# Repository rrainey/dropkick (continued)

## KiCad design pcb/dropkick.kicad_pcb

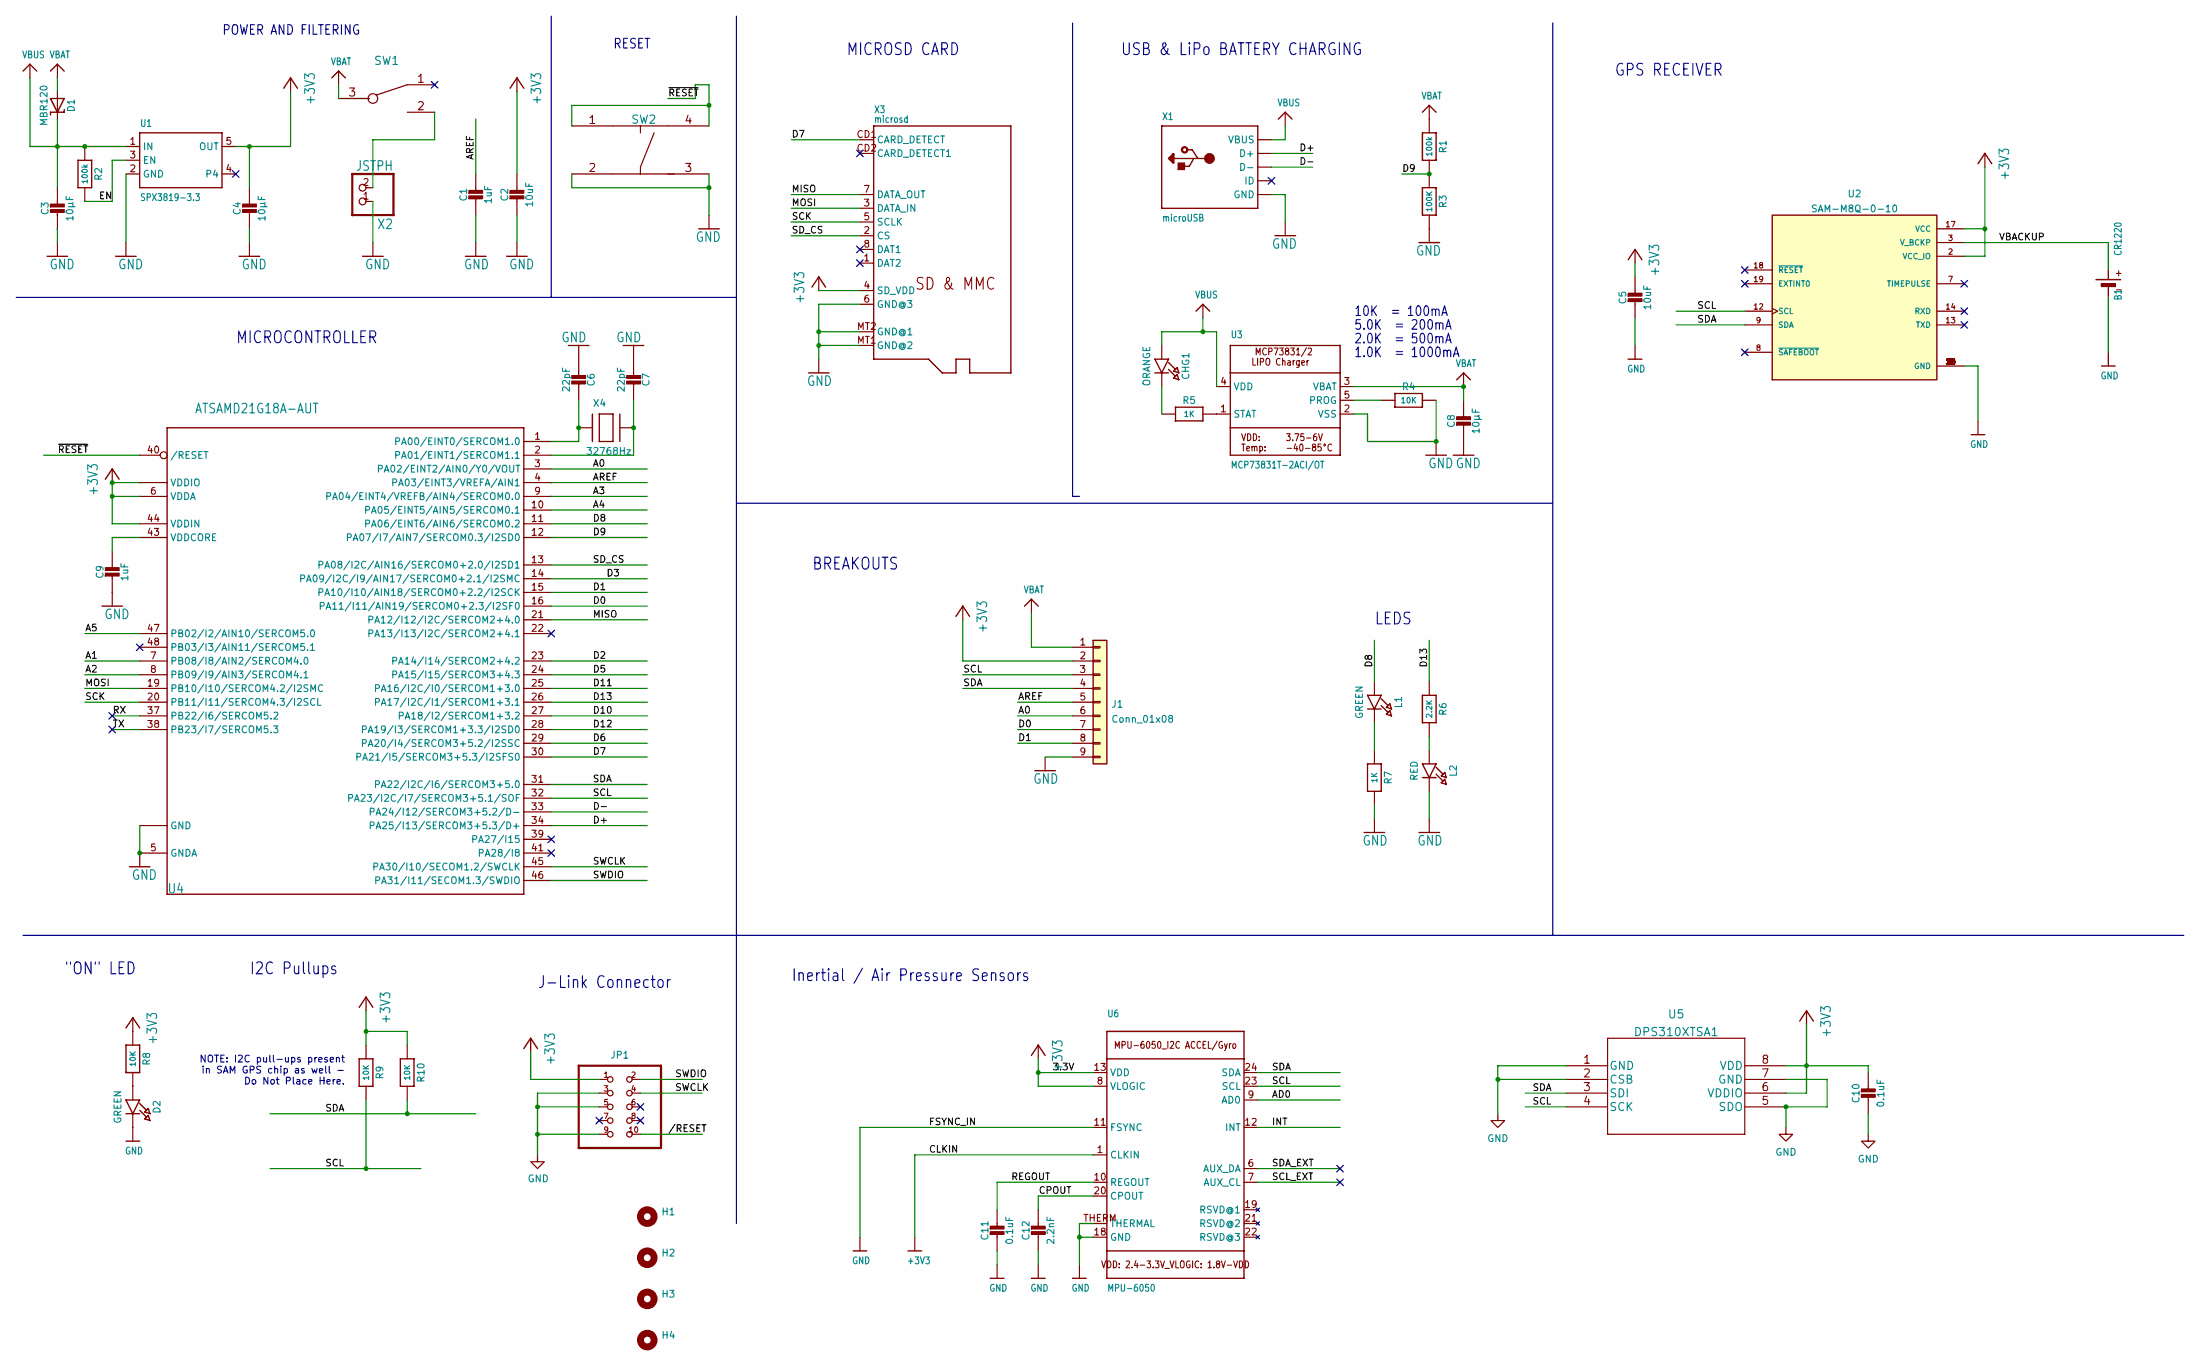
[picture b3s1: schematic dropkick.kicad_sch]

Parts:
B1: CR1220; CR1220-2
C1, C9: 1uF; C_0603_1608Metric
C2, C5: 10uF; C_0805_2012Metric
C3, C4, C8: 10µF; C_0805_2012Metric
C6, C7: 22pF; C_0603_1608Metric
C10: 0.1uF; C_0603_1608Metric
C11: 0.1uF; 0603-NO
C12: 2.2nF; 0603-NO
CHG1: ORANGE; CHIPLED_0603_NOOUTLINE
D1: MBR120; SOD-123
D2: GREEN; CHIPLED_0603_NOOUTLINE
H1, H2, H3, H4: MountingHole; MOUNTINGHOLE_2.5_PLATED
J1: Conn_01x08; PinHeader_1x09_P2.54mm_Vertical
JP1: 3221-10-0300-00-TR
L1: GREEN; CHIPLED_0603_NOOUTLINE
L2: RED; CHIPLED_0603_NOOUTLINE
R1, R2: 100k; 0603-NO
R3: 100K; 0603-NO
R4, R8, R9, R10: 10K; R_0603_1608Metric
R5, R7: 1K; R_0603_1608Metric
R6: 2.2K; R_0603_1608Metric
SW1: 450405020524
SW2: KMR211NG_LFS; KMR211NG LFS
U1: SPX3819-3.3; SOT23-5
U2: SAM-M8Q-0-10; MODULE_SAM-M8Q-0-10; PARTREV R07
U3: MCP73831T-2ACI/OT; SOT23-5
U4: ATSAMD21G18A-AUT; ATSAMD21G15B-AU
U5: DPS310XTSA1
U6: MPU-6050; QFN24_4MM_SMSC
X1: microUSB; 4UCONN_20329_V2
X2: JSTPH; JSTPH2
X3: microsd; MICROSD
X4: 32768Hz; XTAL3215

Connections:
/A0: J1.6, U4.3 (PA02/EINT2/AIN0/Y0/VOUT)
/A1: U4.7 (PB08/I8/AIN2/SERCOM4.0)
/A2: U4.8 (PB09/I9/AIN3/SERCOM4.1)
/A3: U4.9 (PA04/EINT4/VREFB/AIN4/SERCOM0.0)
/A4: U4.10 (PA05/EINT5/AIN5/SERCOM0.1)
/A5: U4.47 (PB02/I2/AIN10/SERCOM5.0)
/AD0: U6.9 (AD0)
/AREF: C1.1, J1.5, U4.4 (PA03/EINT3/VREFA/AIN1)
/CPOUT: C12.1, U6.20 (CPOUT)
/D0: J1.7, U4.16 (PA11/I11/AIN19/SERCOM0+2.3/I2SF0)
/D1: J1.8, U4.15 (PA10/I10/AIN18/SERCOM0+2.2/I2SCK)
/D2: U4.23 (PA14/I14/SERCOM2+4.2)
/D3: U4.14 (PA09/I2C/I9/AIN17/SERCOM0+2.1/I2SMC)
/D5: U4.24 (PA15/I15/SERCOM3+4.3)
/D6: U4.29 (PA20/I4/SERCOM3+5.2/I2SSC)
/D7: U4.30 (PA21/I5/SERCOM3+5.3/I2SFS0), X3.CD1 (CARD_DETECT)
/D8: L1.A, U4.11 (PA06/EINT6/AIN6/SERCOM0.2)
/D9: R1.2, R3.1, U4.12 (PA07/I7/AIN7/SERCOM0.3/I2SD0)
/D10: U4.27 (PA18/I2/SERCOM1+3.2)
/D11: U4.25 (PA16/I2C/I0/SERCOM1+3.0)
/D12: U4.28 (PA19/I3/SERCOM1+3.3/I2SD0)
/D13: R6.1, U4.26 (PA17/I2C/I1/SERCOM1+3.1)
/D+: U4.34 (PA25/I13/SERCOM3+5.3/D+), X1.D+
/D-: U4.33 (PA24/I12/SERCOM3+5.2/D-), X1.D-
/EN: R2.2, U1.3 (EN)
/INT: U6.12 (INT)
/MISO: U4.21 (PA12/I12/I2C/SERCOM2+4.0), X3.7 (DATA_OUT)
/MOSI: U4.19 (PB10/I10/SERCOM4.2/I2SMC), X3.3 (DATA_IN)
/REGOUT: C11.1, U6.10 (REGOUT)
/RX: U4.37 (PB22/I6/SERCOM5.2)
/SCK: U4.20 (PB11/I11/SERCOM4.3/I2SCL), X3.5 (SCLK)
/SCL: J1.3, R9.2, U2.12 (SCL), U4.32 (PA23/I2C/I7/SERCOM3+5.1/SOF), U5.4 (SCK), U6.23 (SCL)
/SCL_EXT: U6.7 (AUX_CL)
/SDA: J1.4, R10.2, U2.9 (SDA), U4.31 (PA22/I2C/I6/SERCOM3+5.0), U5.3 (SDI), U6.24 (SDA)
/SDA_EXT: U6.6 (AUX_DA)
/SD_CS: U4.13 (PA08/I2C/AIN16/SERCOM0+2.0/I2SD1), X3.2 (CS)
/SWCLK: JP1.4, U4.45 (PA30/I10/SECOM1.2/SWCLK)
/SWDIO: JP1.2, U4.46 (PA31/I11/SECOM1.3/SWDIO)
/TX: U4.38 (PB23/I7/SERCOM5.3)
/VBACKUP: B1.+, U2.3 (V_BCKP)
//RESET: JP1.10
/~RESET: SW2.1, SW2.4, U4.40 (/RESET)
unnamed: C6.1, U4.1 (PA00/EINT0/SERCOM1.0), X4.P$1
unnamed: C7.1, U4.2 (PA01/EINT1/SERCOM1.1), X4.P$2
unnamed: C9.1, U4.43 (VDDCORE)
unnamed: CHG1.C, R5.1
unnamed: D2.A, R8.2
unnamed: L1.C, R7.1
unnamed: L2.A, R6.2
unnamed: R4.1, U3.5 (PROG)
unnamed: R5.2, U3.1 (STAT)
unnamed: SW1.2, X2.2
VBAT: C8.1, D1.A, J1.1, R1.1, SW1.3, U3.3 (VBAT)
VBUS: C3.1, CHG1.A, D1.C, R2.1, U1.1 (IN), U3.4 (VDD), X1.VBUS

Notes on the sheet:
GPS RECEIVER
"ON" LED
I2C Pullups
10K = 100mA
Inertial / Air Pressure Sensors
MICROCONTROLLER
1.0K = 1000mA
5.0K = 200mA
BREAKOUTS
RESET
POWER AND FILTERING
J-Link Connector
LEDS
2.0K = 500mA
MICROSD CARD
USB & LiPo BATTERY CHARGING
NOTE: I2C pull-ups present in SAM GPS chip as well - Do Not Place Here.

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
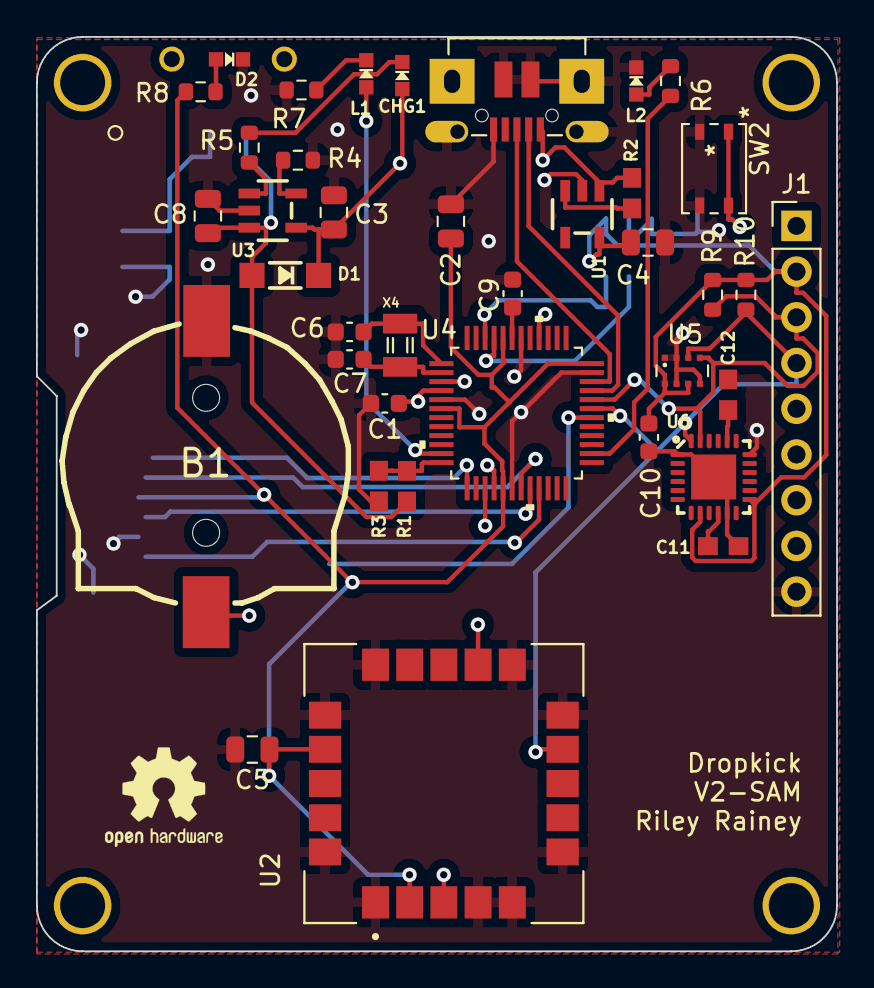
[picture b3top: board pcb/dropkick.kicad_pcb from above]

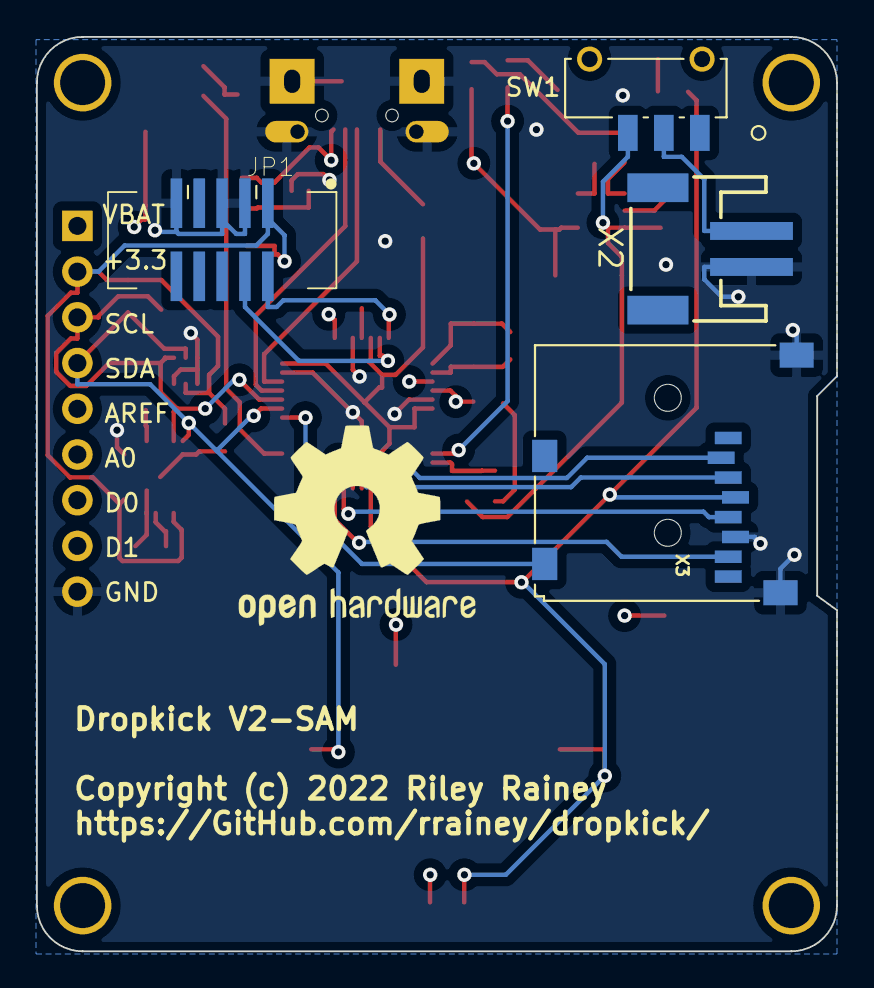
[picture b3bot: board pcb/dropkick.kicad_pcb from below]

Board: 4 copper layers, 44.5 x 50.8 mm, 48 parts (5 on the bottom side), 37 nets.

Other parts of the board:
REF1: OSHW-Logo2_14.6x12mm_SilkScreen
REF2: OSHW-Logo2_7.3x6mm_SilkScreen

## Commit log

2022-01-22 inital directory structure
2022-01-24 Add 3d PCB model and updated main image
2022-01-24 Add PDF of schematic
2022-01-26 Add u-block CAM-M8Q symbol and footprint
2022-01-26 Update keepout on CAM-M8C
2022-01-26 Correct CAM-M8C footprint
2022-01-28 V3 board
2022-01-28 Add u-blox CAM STEP model
2022-01-29 Alternate REG IC
2022-01-29 IC substitutions
2022-01-29 Remove .rules freerouting file
2022-01-30 Reorganize footprint libraries
2022-01-30 Add enclosure printing notes
2022-02-21 Add BOM, minor footprint fixes
2022-03-01 Tweak BOM, add MFR part numbers
2022-03-03 update schematic PDF
2022-03-08 V4 board candidate
2022-03-15 V2-SAM working draft
2022-03-15 test of 4-layer PCB
2022-03-22 V2-SAM PCB; now back to 2 layers
2022-05-01 Add PCB/reflow notes
2022-05-01 Edit typo
2022-05-01 Improve reflow narrative and ignore VS Code configuration files
2022-05-01 Add reflow profile image to README
2022-05-01 Update chip shortage section
2022-05-02 add PCB definitions for both SAM and CAM variants
2022-05-03 update chip shortage info
2022-05-03 Add explanation of the two PCB folders
2022-05-03 README update
2022-05-03 add u-blox URLs
2022-05-03 update mfr reference
2022-05-03 add gerber files
2022-05-19 Small edit
2022-07-10 Added altitude-based static testing to verify app state control
2022-07-17 new test baseline
2022-07-17 first u-blox baseline
2022-07-17 first dropkick flight test version
2022-07-23 add time hack messages
2022-07-23 add JUMPING state
2022-07-23 add weight information
2022-07-23 GNSS sampling now 2Hz during jump
2022-07-30 add documentation of log file structure
2022-07-30 fix typos in log file readme
2022-07-31 expand the log file documentation
2022-07-31 Starter axes file
2022-08-01 updated enclosure and enhanced SAM-M8 footprint
2022-08-01 add diagram for IMU axes
2022-08-02 V3-SAM gerber files
2022-08-02 starter analysis files
2022-08-02 Test LaTeX markdown
2022-08-02 Update equations to add R-004-1992
2022-08-03 Add quaternion initialization.
2022-08-04 Clean up ANALYSIS notes
2022-08-04 add strapdown flow image
2022-08-05 fix typo
2022-08-05 save experiments
2022-08-06 firmware version 53; see code for details
2022-08-13 Add images
2022-08-14 checkin untested baseline of initial analysis code
2022-08-14 latest Modeler baseline
2022-08-15 fresh baseline with license headers
2022-08-16 version 54 of firmware; ensure increase in GNSS sampling rate
2022-08-16 first try at 3-pass approach
2022-08-18 testing pose reconstruction code
2022-08-18 add status update to README
2022-08-18 add comments on execution
2022-08-18 latest baseline.
2022-08-19 estimate initial Dropkick orientation on jumper
2022-08-19 latest test baseline. focus on strapdown phase.
2022-08-21 Add testing function and Quaternion class
2022-08-22 improved Quaternion class
2022-08-22 add test data set
2022-08-22 add test data
2022-08-22 overload display function
2022-08-28 firmware version 55
2022-09-03 refine Quaternion mtimes
2022-09-03 add ability to plot altitude and acceleration together
2022-09-03 add brief status updates
2022-09-03 add smaller exploding diagram
2022-09-03 add exploding disassembly animation
2022-09-04 fixed a typo
2023-02-18 use internal antenna only
2023-08-09 v3 SAM PCB
2023-08-12 V4 SAM PCB
2023-08-15 V4 SAM
2023-09-13 V4 SAM PCB notes
2023-09-22 Updated enclosure for V4 PCB
    Includes USB-C clearance
2023-09-27 Update paste margins on ICM42688; minor pcb trace
2023-10-01 V5-CAM PCB
2023-10-01 V5-CAM add INT line to MPU6050
2023-10-02 Clean up AD0 address line for MPU6050
2023-10-02 Fix MPU6050 footprint; gerber plot
2023-10-02 Improve LED wiring consistency; update gerber
2023-10-02 Add mfr info
2023-10-02 Add VLOGIC bypass cap to 6050; update gerbers
2023-10-03 Upgrade to KiCad 7
2023-10-03 add STEP image
2023-10-03 Switch to 2.0mm pads and added SWDIO/SWCLK pads to flash w/o header
2023-10-04 Update new enclosure to prevent closing hang-ups
2023-10-04 Added extra CAP per DPS310 datasheet
2023-10-04 Add boxes to schematic; clean up PCB placement; use PCBWay gerber settings
2023-10-06 Update switch
2023-10-15 Add presets
2023-10-15 Add bootloader information
2023-10-17 Add Changelog
2023-11-25 doc updates
2024-02-10 Add Test Sketch for SAM V4
2024-02-24 various minor updates
2024-11-14 Update log documents to version 56/156
2024-11-14 Add Temp frames diagram
2024-11-14 Refine some documentation
2024-11-14 Doc refinements
2024-11-14 a few typos are fixed
